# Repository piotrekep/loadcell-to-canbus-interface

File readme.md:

# Digital Scale with CAN Bus

This repository contains firmware for a digital scale system based on the ATmega328 microcontroller. Developed over 10 years ago, this project reads analog data via an ADS1234 ADC and transmits measurements over a CAN bus using an MCP2515 controller through an SPI interface.

## Overview

The firmware implements a digital weighing system that:

- **Acquires Data**: Reads four channels of analog data from an ADS1234 ADC.
- **CAN Bus Communication**: Transmits the acquired data in two separate CAN messages (IDs 0x250 and 0x251).
- **SPI Interface**: Uses custom SPI routines to communicate with both the CAN controller and the ADS1234.
- **Robust Operation**: Utilizes a watchdog timer and interrupt-driven routines to ensure reliable operation.

## Hardware Setup

### ATmega328
- **Microcontroller**: ATmega328
- **Clock Speed**: 20 MHz (FOSC = 20,000,000)

### ADS1234 ADC
- **Data Acquisition**:
  - **Input Selection**: Controlled via two pins on PORTC (A0 on PC1 and A1 on PC0).
  - **Gain Control**: Connected to PORTD (GAIN0 on PD1 and GAIN1 on PD2).
  - **Speed Control**: Connected to PC5.
  - **Data**: Read from PC2.
  - **Clock**: Driven from PC3.
  - **Power**: Controlled on PC4.
- **Channel Selection**: Four channels are read sequentially, with channels AIN1–AIN4 selected via software.

### CAN Bus (MCP2515)
- **Communication**: Uses the SPI interface.
  - **MOSI**: PB3
  - **SCK**: PB5
  - **Chip Select (CS)**: PB2
- **CAN Messaging**: Two messages are prepared and sent:
  - **Message 1 (ID 0x250)**: Contains data from channels AIN1 and AIN2.
  - **Message 2 (ID 0x251)**: Contains data from channels AIN3 and AIN4.

### UART (Debugging)
- **Serial Communication**: Basic serial routines are provided for debugging using UART0 at 115200 baud.

## Project Structure

```
.
├── ads1234/
│   ├── ads1234.c
│   └── ads1234.h
├── CAN_drv/
│   ├── can_drv.c
│   └── can_drv.h
├── SPI_drv/
│   └── SPIm328.c
├── twi/             (if applicable)
│   └── twi.c
├── uartsimple/
│   ├── uartsimple.c
│   └── usartsimple.h
├── types/
│   └── tdef.h
└── main.c
```

## Build Instructions

This project is configured for the AVR-GCC toolchain and was originally built using Atmel AVR Studio. Two build configurations are provided:

- **Debug**: Compiled with debugging symbols and optimization level O1.
- **Release**: Compiled with optimizations for size (-Os).

To compile the project from the command line, you might use:

```bash
avr-gcc -mmcu=atmega328p -Os -DF_CPU=20000000UL -o digital_scale.elf \
  main.c ads1234/ads1234.c CAN_drv/can_drv.c SPI_drv/SPIm328.c uartsimple/uartsimple.c
avr-objcopy -O ihex -R .eeprom digital_scale.elf digital_scale.hex
```

Be sure to adjust include paths and source files as needed.

## Flashing the Firmware

You can use your preferred AVR programmer (such as avrdude) to flash the firmware. For example:

```bash
avrdude -c usbtiny -p m328p -U flash:w:digital_scale.hex:i
```

## Configuration Details

- **Clock Speed**: Set to 20 MHz.
- **UART Baud Rate**: 115200 baud.
- **CAN Bus Baud Rate**: Configured using the `CAN_setBaud20` function. Baud rate options include 125, 250, and 500 kbps.
- **Watchdog Timer**: Enabled with a 2-second timeout to help ensure robust operation.

## PCB and Schematics

PCB layout and schematic files are located in the `wagapcb` directory. Multiple revisions exist:

- **waga**: Original layout files (`waga_can.brd`, `waga_can.sch`, and associated Gerber outputs).
- **waga v0.1**: First revision of the board, containing minor tweaks to layout and connectivity.
- **waga v0.2**: Second revision with updates for component placement and routing improvements.
- **waga v0.2stm**: A variant of the second revision intended for further prototyping.

Each folder contains EAGLE project files (`.brd`, `.sch`) and Gerber files (`.GBL`, `.GBO`, `.GTL`, etc.) for manufacturing. 

## Notes

- This project is a legacy codebase and may require updates for modern toolchains or hardware revisions.
- Detailed configuration settings (such as ADC channel selection and CAN bus setup) can be found within the source code files.

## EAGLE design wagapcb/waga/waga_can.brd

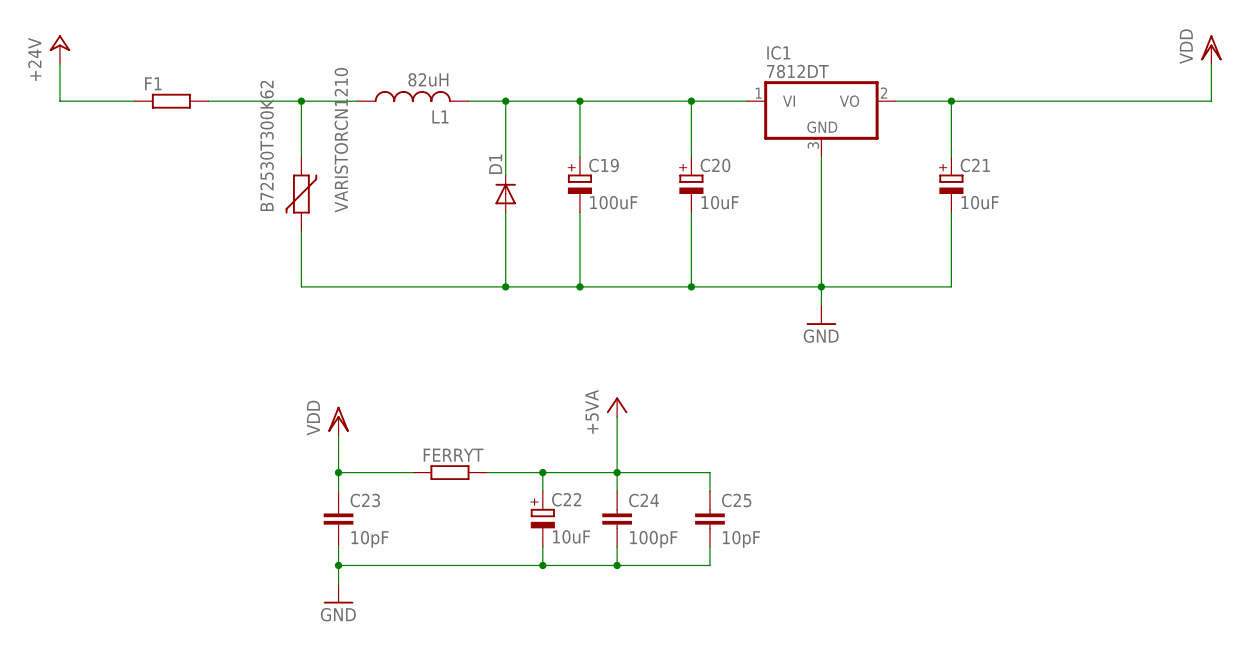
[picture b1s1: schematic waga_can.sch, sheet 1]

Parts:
B72530T300K62: VARISTORCN1210; CT/CN1210
C19: 100uF; 153CLV-0810
C20, C21, C22: 10uF; 153CLV-0605
C23, C25: 10pF; C0805
C24: 100pF; C0805
D1: DIODE-SMB; SMB
F1: R-EU_1812X7R; 1812X7R
FERRYT: R-EU_M0805; M0805
IC1: 7812DT; TO252
L1: 82uH; L4532P

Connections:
+5V: C22.+, C24.1, C25.1, FERRYT.2; also elsewhere on the board
+24V: F1.1; also elsewhere on the board
GND: B72530T300K62.2, C19.-, C20.-, C21.-, C22.-, C23.2, C24.2, C25.2, D1.A, IC1.3 (GND); also elsewhere on the board
unnamed: C19.+, C20.+, D1.C, IC1.1 (VI), L1.2
unnamed: B72530T300K62.1, F1.2, L1.1
VDD: C21.+, C23.1, FERRYT.1, IC1.2 (VO); also elsewhere on the board

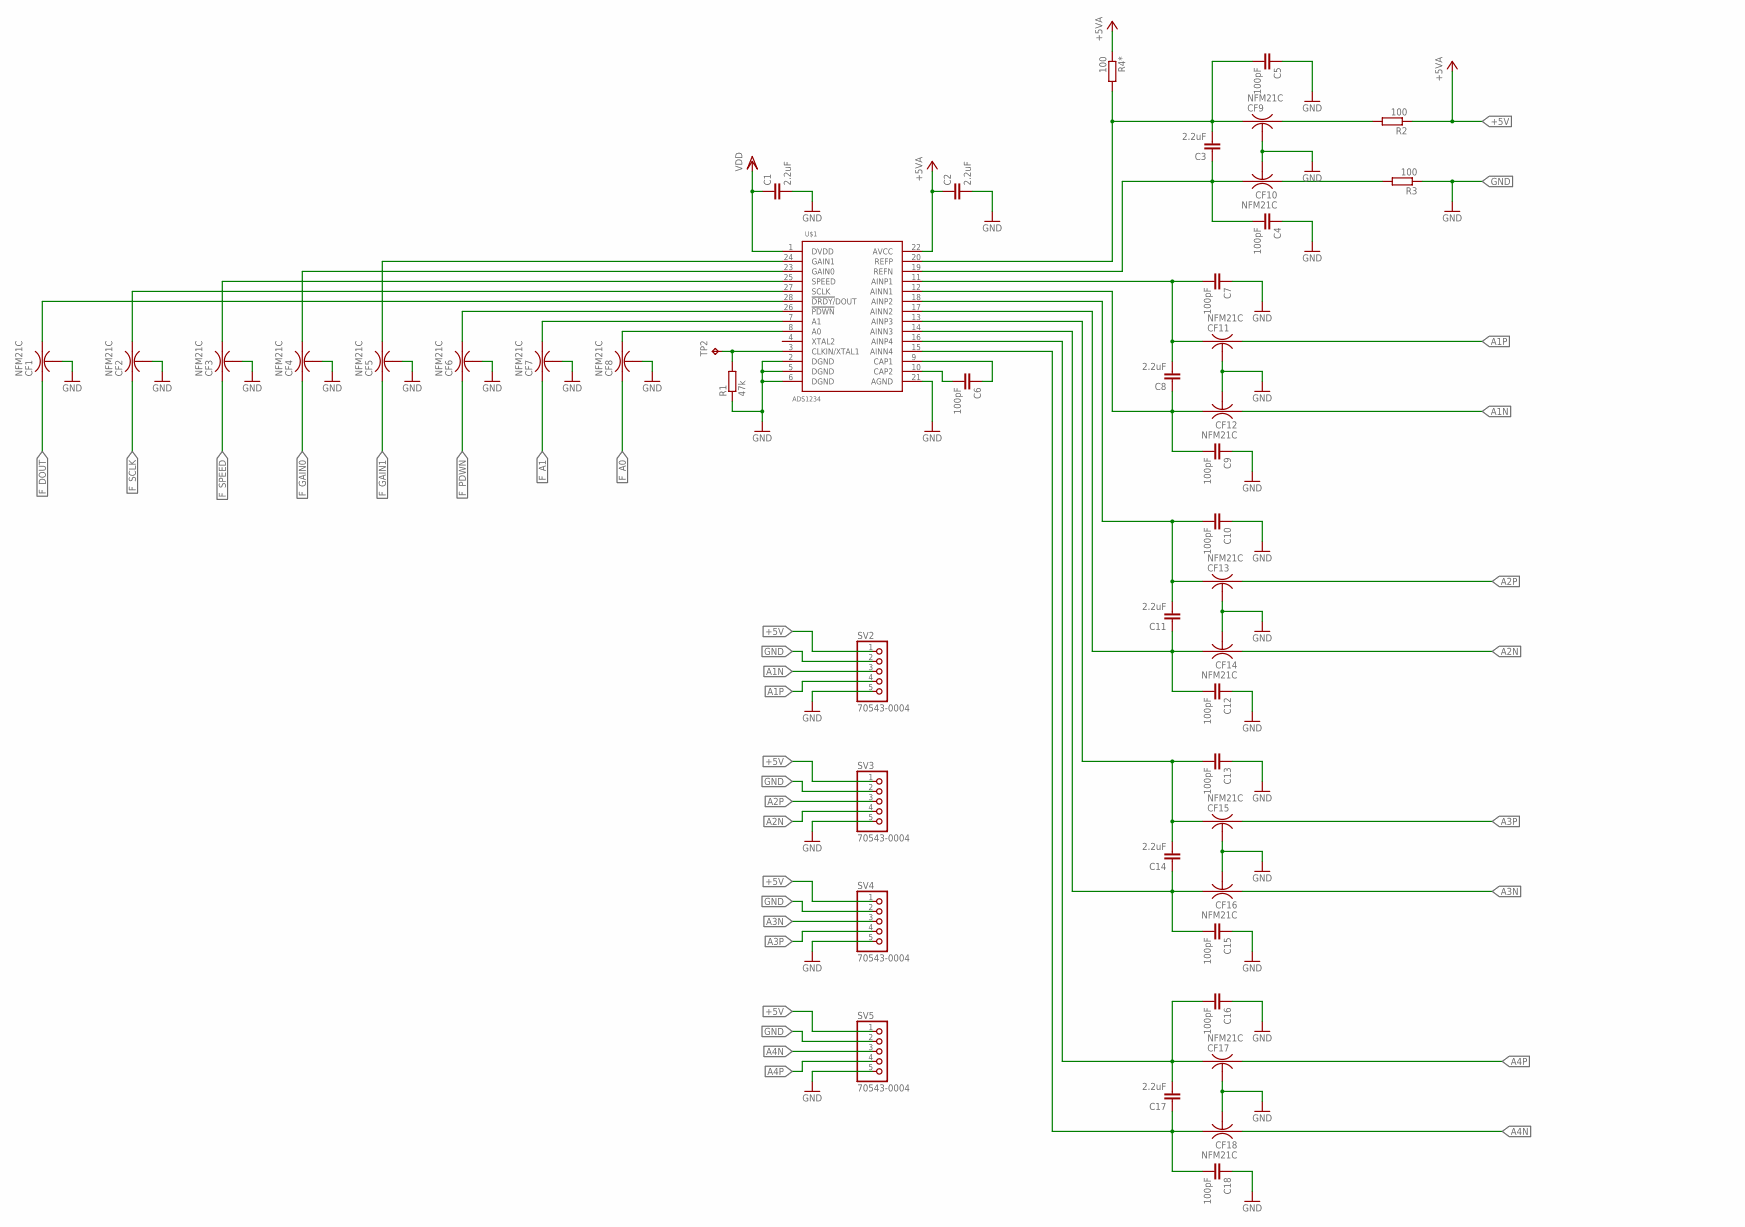
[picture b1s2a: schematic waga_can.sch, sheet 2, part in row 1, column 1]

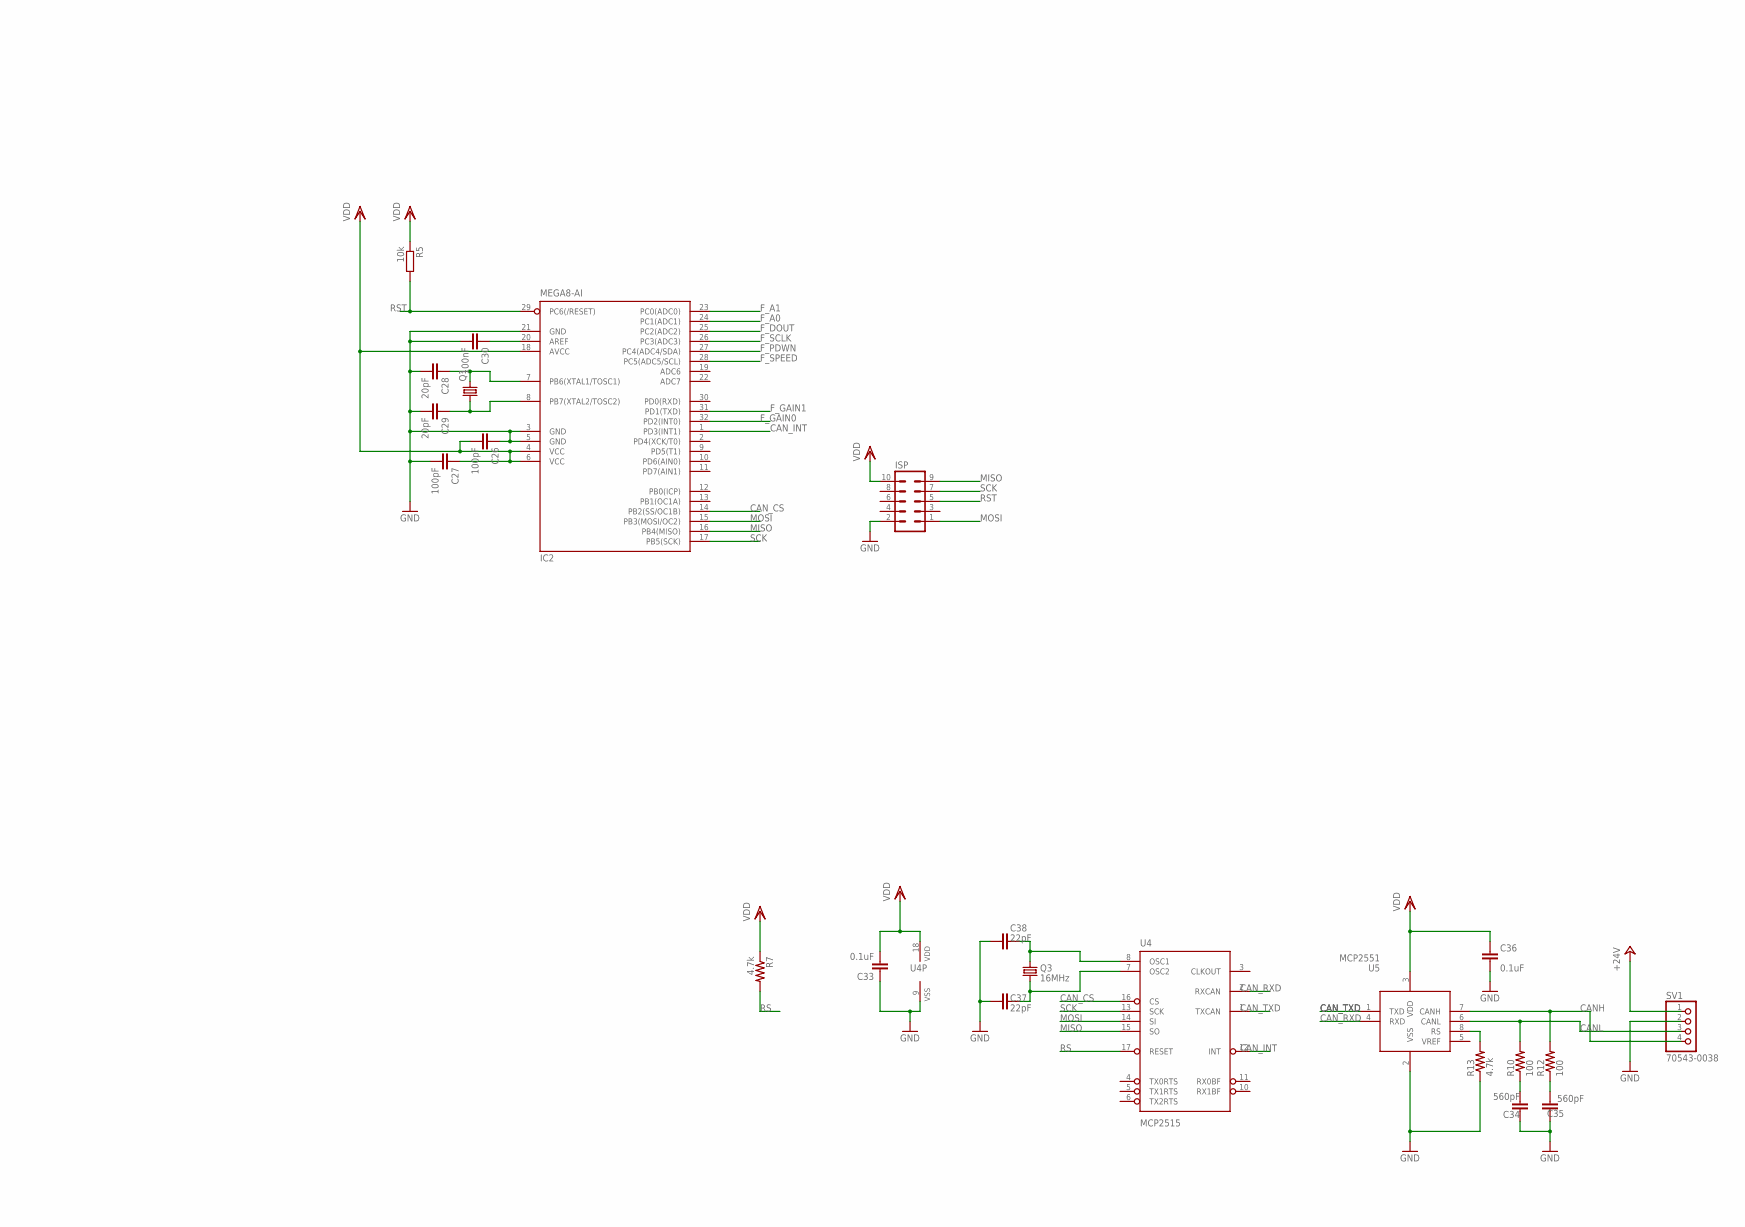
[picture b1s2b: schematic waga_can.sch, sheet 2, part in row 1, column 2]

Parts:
C1, C2, C3, C8, C11, C14, C17: 2.2uF; C0805K
C4, C5, C6, C7, C9, C10, C12, C13, C15, C16, C18: 100pF; C0603
C26, C27: 100pF; C0805K
C28, C29: 20pF; C0805K
C30: 100nF; C0805K
C33, C36: 0.1uF; 0603-CAP
C34, C35: 560pF; 0603-CAP
C37, C38: 22pF; 0603-CAP
CF1, CF2, CF3, CF4, CF5, CF6, CF7, CF8, CF9, CF10, CF11, CF12, CF13, CF14, CF15, CF16, CF17, CF18: NFM21C
IC2: MEGA8-AI; TQFP32-08
ISP: ML10
Q1: CRYSTALCTS406; CTS406
Q3: 16MHz; CRYSTAL-SMD-5X3
R1: 47k; R0805
R2, R3, R4*: 100; R0805
R5: 10k; R0805
R7, R13: 4.7k; 0603-RES
R10, R12: 100; 0603-RES
SV1: 70543-0038
SV2, SV3, SV4, SV5: 70543-0004
TP2: TPTP06R; TP06R
U4: MCP2515; SO-18W
U5: MCP2551; SO-08M
U$1: ADS1234; TSSOP-28

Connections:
+5V: C2.1, R2.1, R4*.1, SV2.1, SV3.1, SV4.1, SV5.1, U$1.22 (AVCC); also elsewhere on the board
+24V: SV1.1; also elsewhere on the board
A0: CF8.3, U$1.8 (A0)
A1: CF6.3, U$1.26 (!PDWN)
A1N: CF12.1, SV2.3
A1P: CF11.3, SV2.4
A2N: CF14.1, SV3.4
A2P: CF13.3, SV3.3
A3N: CF16.1, SV4.3
A3P: CF15.3, SV4.4
A4N: CF18.1, SV5.3
A4P: CF17.3, SV5.4
CANH: R12.2, SV1.4, U5.7 (CANH)
CANL: R10.2, SV1.3, U5.6 (CANL)
CAN_CS: IC2.14 (PB2(SS/OC1B)), U4.16 (CS)
CAN_INT: IC2.1 (PD3(INT1)), U4.12 (INT)
CAN_RXD: U4.2 (RXCAN), U5.4 (RXD)
CAN_TXD: U4.1 (TXCAN), U5.1 (TXD)
DOUT: CF1.3, U$1.28 (!DRDY/!DOUT)
F_A0: CF8.1, IC2.24 (PC1(ADC1))
F_A1: CF7.1, IC2.23 (PC0(ADC0))
F_DOUT: CF1.1, IC2.25 (PC2(ADC2))
F_GAIN0: CF4.1, IC2.32 (PD2(INT0))
F_GAIN1: CF5.1, IC2.31 (PD1(TXD))
F_PDWN: CF6.1, IC2.27 (PC4(ADC4/SDA))
F_SCLK: CF2.1, IC2.26 (PC3(ADC3))
F_SPEED: CF3.1, IC2.28 (PC5(ADC5/SCL))
GAIN0: CF4.3, U$1.23 (GAIN0)
GAIN1: CF5.3, U$1.24 (GAIN1)
GND: C1.2, C2.2, C4.1, C5.1, C7.1, C9.1, C10.1, C12.1, C13.1, C15.1, C16.1, C18.1, C26.1, C27.2, C28.2, C29.2, C30.2, C33.1, C34.1, C35.1, C36.1, C37.1, C38.1, CF1.2@1 (2), CF1.2@2 (2), CF2.2@1 (2), CF2.2@2 (2), CF3.2@1 (2), CF3.2@2 (2), CF4.2@1 (2), CF4.2@2 (2), CF5.2@1 (2), CF5.2@2 (2), CF6.2@1 (2), CF6.2@2 (2), CF7.2@1 (2), CF7.2@2 (2), CF8.2@1 (2), CF8.2@2 (2), CF9.2@1 (2), CF9.2@2 (2), CF10.2@1 (2), CF10.2@2 (2), CF11.2@1 (2), CF11.2@2 (2), CF12.2@1 (2), CF12.2@2 (2), CF13.2@1 (2), CF13.2@2 (2), CF14.2@1 (2), CF14.2@2 (2), CF15.2@1 (2), CF15.2@2 (2), CF16.2@1 (2), CF16.2@2 (2), CF17.2@1 (2), CF17.2@2 (2), CF18.2@1 (2), CF18.2@2 (2), IC2.3 (GND), IC2.5 (GND), IC2.21 (GND), ISP.2, R1.1, R3.1, R13.1, SV1.2, SV2.2, SV2.5, SV3.2, SV3.5, SV4.2, SV4.5, SV5.2, SV5.5, U4.9 (VSS), U5.2 (VSS), U$1.2 (DGND), U$1.5 (DGND), U$1.6 (DGND), U$1.21 (AGND); also elsewhere on the board
MISO: IC2.16 (PB4(MISO)), ISP.9, U4.15 (SO)
MOSI: IC2.15 (PB3(MOSI/OC2)), ISP.1, U4.14 (SI)
unnamed: C30.1, IC2.20 (AREF)
unnamed: C34.2, R10.1
unnamed: CF7.3, U$1.7 (A1)
unnamed: C28.1, IC2.7 (PB6(XTAL1/TOSC1)), Q1.3 (2)
unnamed: R1.2, TP2.TP, U$1.3 (CLKIN/XTAL1)
unnamed: C29.1, IC2.8 (PB7(XTAL2/TOSC2)), Q1.1
unnamed: C3.2, C5.2, CF9.1, R4*.2, U$1.20 (REFP)
unnamed: C3.1, C4.2, CF10.3, U$1.19 (REFN)
unnamed: C14.1, C15.2, CF16.3, U$1.14 (AINN3)
unnamed: CF9.3, R2.2
unnamed: CF10.1, R3.2
unnamed: C6.2, U$1.10 (CAP2)
unnamed: C6.1, U$1.9 (CAP1)
unnamed: C35.2, R12.1
unnamed: C7.2, C8.2, CF11.1, U$1.11 (AINP1)
unnamed: C8.1, C9.2, CF12.3, U$1.12 (AINN1)
unnamed: C10.2, C11.2, CF13.1, U$1.18 (AINP2)
unnamed: C11.1, C12.2, CF14.3, U$1.17 (AINN2)
unnamed: R13.2, U5.8 (RS)
unnamed: C13.2, C14.2, CF15.1, U$1.13 (AINP3)
unnamed: C38.2, Q3.3 (2), U4.8 (OSC1)
unnamed: C37.2, Q3.1, U4.7 (OSC2)
unnamed: C16.2, C17.2, CF17.1, U$1.16 (AINP4)
unnamed: C17.1, C18.2, CF18.3, U$1.15 (AINN4)
RS: R7.2, U4.17 (RESET)
RST: IC2.29 (PC6(/RESET)), ISP.5, R5.2
SCK: IC2.17 (PB5(SCK)), ISP.7, U4.13 (SCK)
SCLK: CF2.3, U$1.27 (SCLK)
SPEED: CF3.3, U$1.25 (SPEED)
VDD: C1.1, C26.2, C27.1, C33.2, C36.2, IC2.4 (VCC), IC2.6 (VCC), IC2.18 (AVCC), ISP.10, R5.1, R7.1, U4.18 (VDD), U5.3 (VDD), U$1.1 (DVDD); also elsewhere on the board

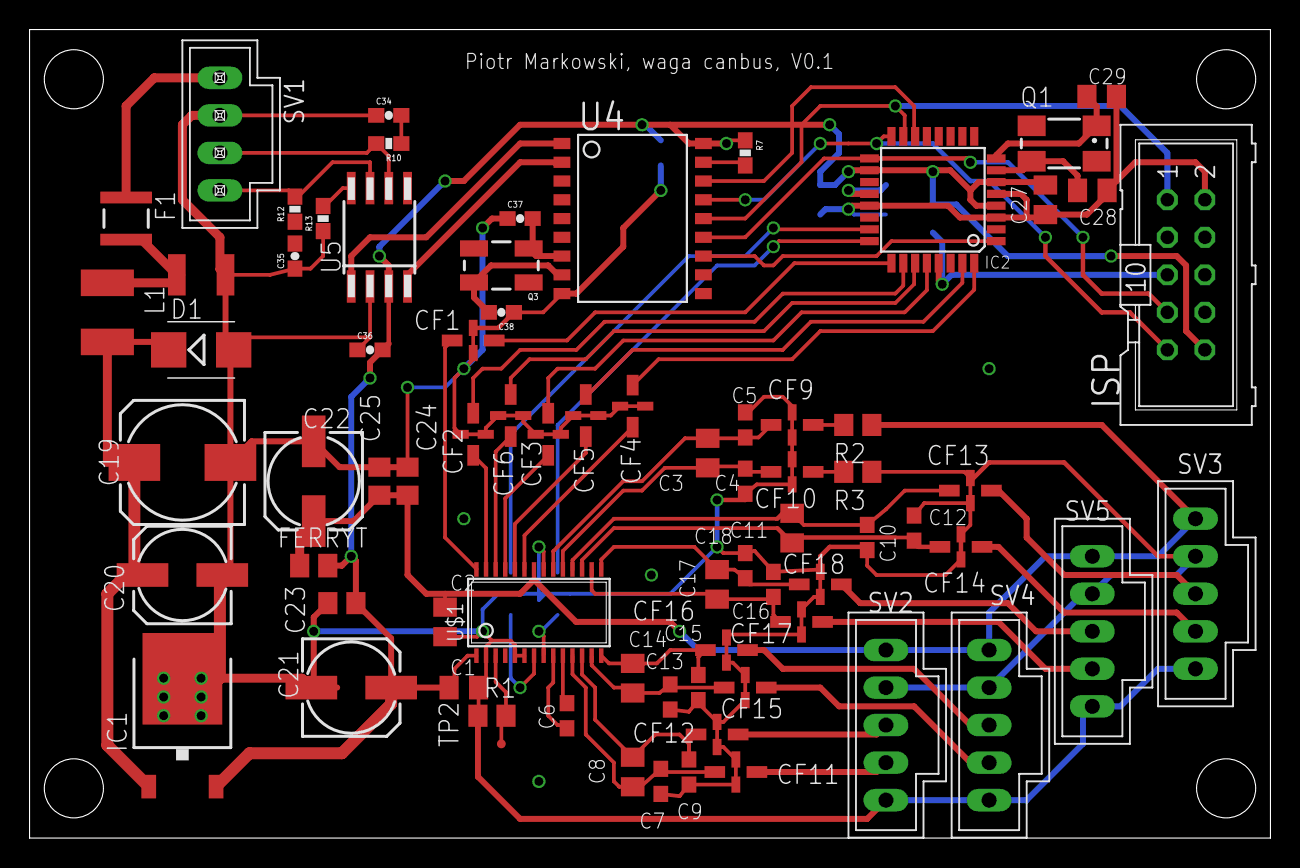
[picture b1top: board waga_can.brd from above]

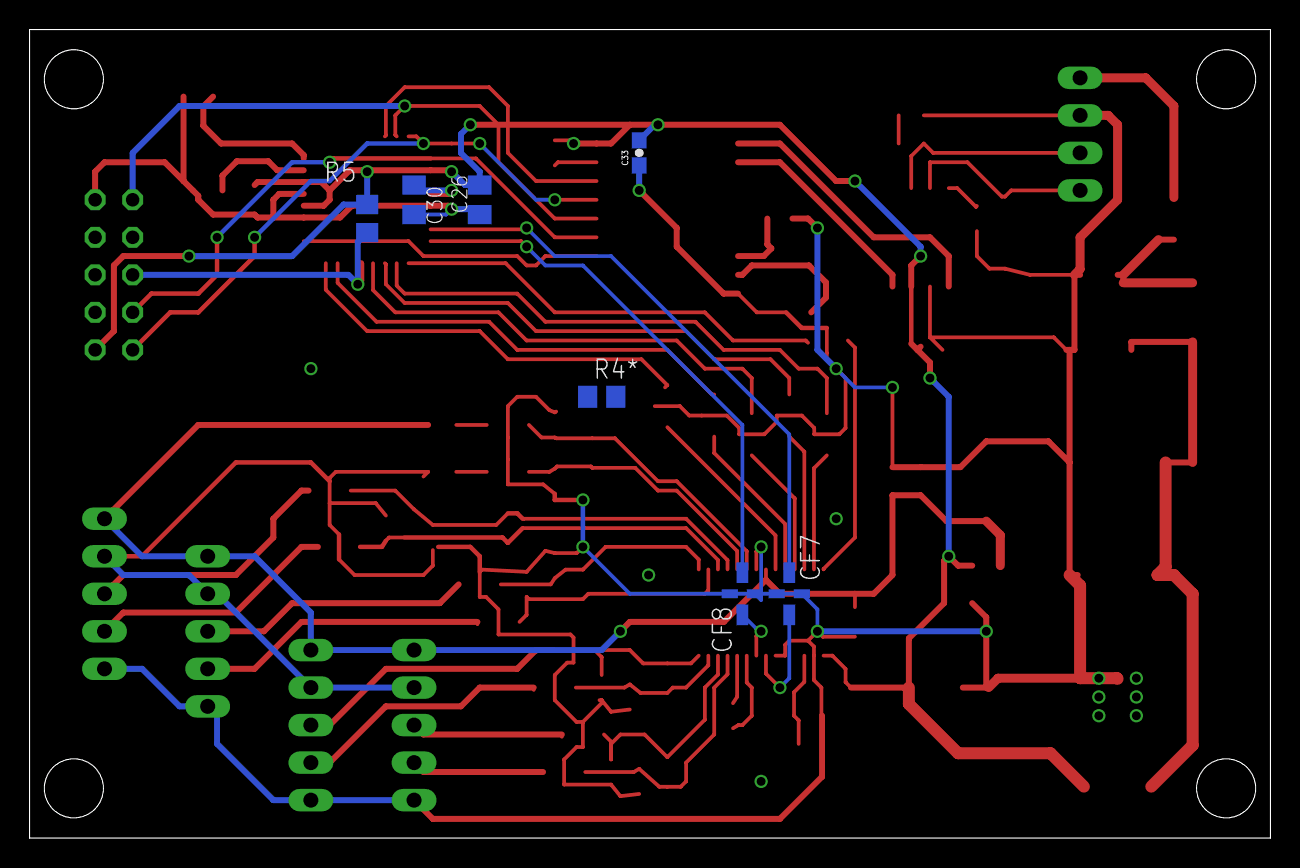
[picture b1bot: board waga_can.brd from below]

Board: 2 copper layers, 84.0 x 54.7 mm, 82 parts (7 on the bottom side), 64 nets.

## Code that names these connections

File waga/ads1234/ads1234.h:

/*
 * ads1234.h
 *
 * Created: 2017-06-29 14:13:18
 *  Author: Ja
 */ 


#ifndef ADS1234_H_
#define ADS1234_H_

#include <inttypes.h>
#include <avr/io.h>

#define GAIN0_PORT PORTD
#define GAIN1_PORT PORTD
#define GAIN0_PIN 1
#define GAIN1_PIN 2
#define GAIN0_DDR DDRD
#define GAIN1_DDR DDRD


#define A0_PORT PORTC
#define A1_PORT PORTC
#define A0_PIN 1
#define A1_PIN 0
#define A0_DDR DDRC
#define A1_DDR DDRC

#define SPEED_PORT PORTC
#define SPEED_PIN 5
#define SPEED_DDR DDRC

#define DATA_PORT PINC
#define DATA_PIN 2
#define DATA_DDR DDRC

#define CLK_PORT PORTC
#define CLK_PIN 3
#define CLK_DDR DDRC


#define PWR_PORT PORTC
#define PWR_PIN 4
#define PWR_DDR DDRC



#define ADS1234_AIN1 0
#define ADS1234_AIN2 2
#define ADS1234_AIN3 1
#define ADS1234_AIN4 3


#define ADS1234_GAIN1 0
#define ADS1234_GAIN2 2
#define ADS1234_GAIN64 1
#define ADS1234_GAIN128 3


#define ADS1234_LOW_SPEED 0
#define ADS1234_HIGH_SPEED 1


#define ADS1234_PWR_ON 1
#define ADS1234_PWR_OFF 0

void ADS1234_init(void);
void ADS1234_PWR(uint8_t stat);
void ADS1234_input_select(uint8_t input);
void ADS1234_gain_select(uint8_t gain);
void ADS1234_Speed(uint8_t spd);
uint32_t ADS1234_read(void);
void ADS1234_clk_high(void);
void ADS1234_clk_low(void);

#endif /* ADS1234_H_ */

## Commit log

2025-02-16 pierwszy commit
2025-02-16 a little cleanup and readme
2025-03-24 added pcb and schematic
